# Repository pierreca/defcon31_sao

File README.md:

# DEFCON 31 SAO

* `3d_models`: 3mf files exported from Shapr3d, these models were 3d printed to build the SAO
*  `pcb`: KiCad project (ultra simplistic) that was used to have the circuit board made by Oshpark

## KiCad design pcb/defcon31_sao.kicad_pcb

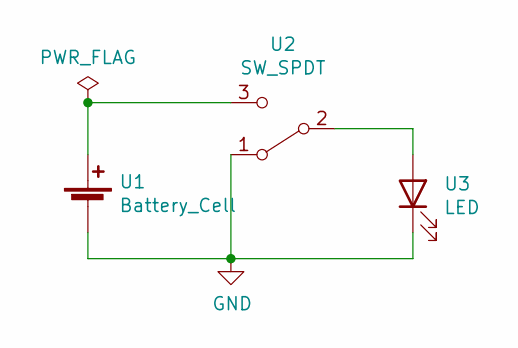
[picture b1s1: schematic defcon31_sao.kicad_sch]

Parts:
U1: Battery_Cell; BatteryHolder_Keystone_3000_1x12mm
U2: SW_SPDT; SW_SPDT_PCM12
U3: LED; LED_D5.0mm_FlatTop

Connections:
GND: U1.2 (-), U2.1 (A), U3.1 (K)
unnamed: U1.1 (+), U2.3 (C)
unnamed: U2.2 (B), U3.2 (A)

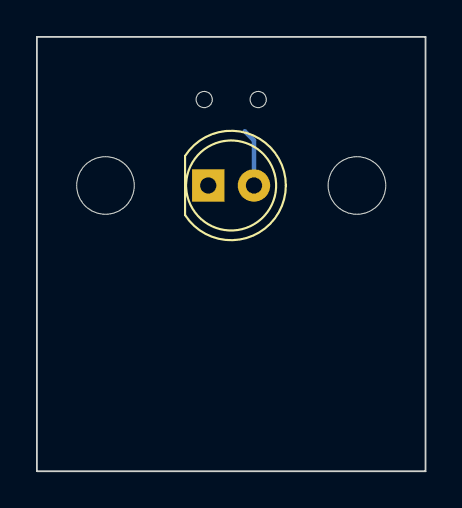
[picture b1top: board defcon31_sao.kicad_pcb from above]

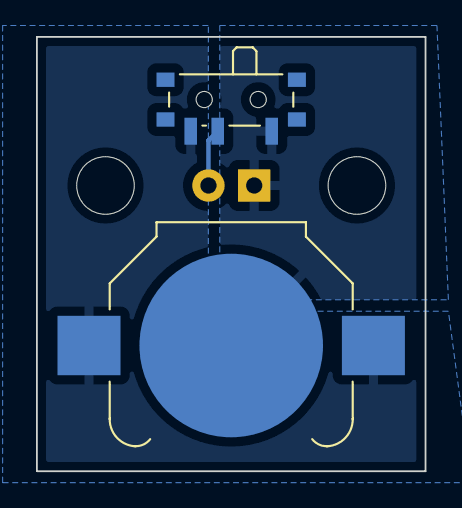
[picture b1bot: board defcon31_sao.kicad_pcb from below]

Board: 2 copper layers, 21.6 x 24.1 mm, 3 parts (2 on the bottom side), 3 nets.
